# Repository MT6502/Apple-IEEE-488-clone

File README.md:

# Apple-IEEE-488-clone
the schematic is based on the original documented
in the IEEE-488 interface manual from Apple with some smaller changes, mainly for easier routing the board.
The manual can be found at several places in the internet. 
Actually the following links will work:
https://www.applefritter.com/files/2021/08/15/Apple%20%5D%5B%20___%20IEEE-488%20Interface%20Users%20Guide.pdf
the rom can be found here, no other source found yet:
https://www.applefritter.com/files/2021/09/19/Apple%20IEEE%20488%20ROM%20Dump.BIN_.zip
corosponnding chat @Applefritter:
https://www.applefritter.com/content/apple-ieee-488-interface-card

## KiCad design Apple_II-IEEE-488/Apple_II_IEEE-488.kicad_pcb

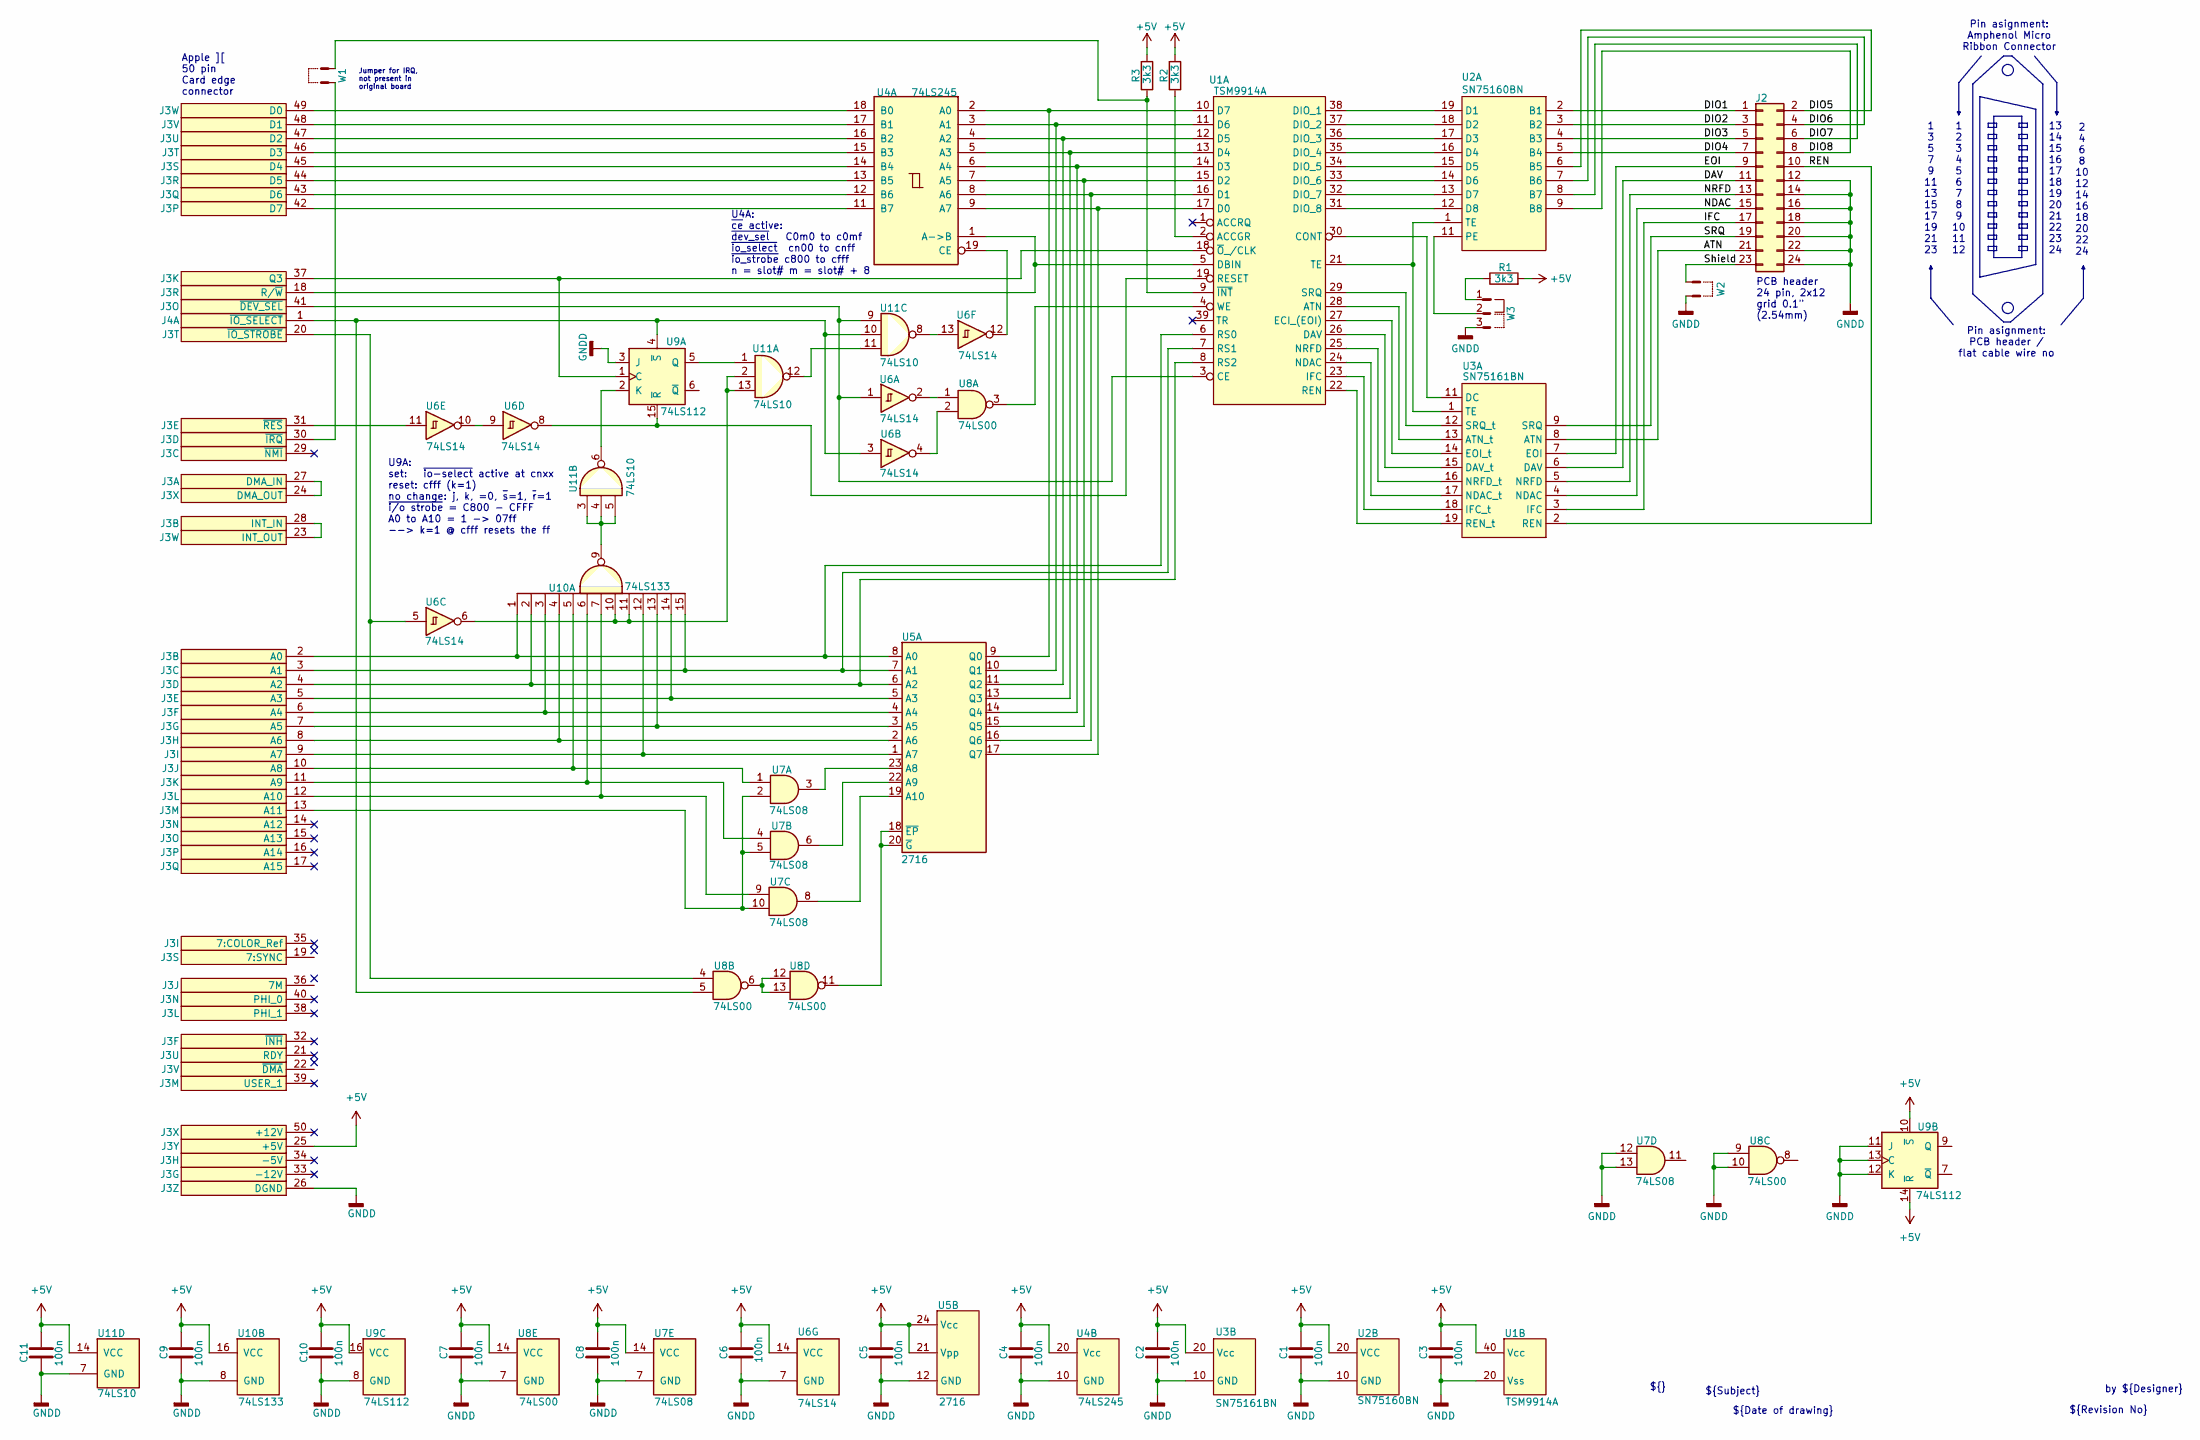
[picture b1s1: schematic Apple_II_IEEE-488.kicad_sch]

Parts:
C1, C2, C3, C4, C5, C6, C7, C8, C9, C10, C11: 100n; C_disk_2.54mm
J2: Conn_02x12_Odd_Even; IDC-Header_2x12_P2.54mm_Vertical
J3: Apple_II_card_edge
J4: (no value)
R1, R2, R3: 3k3; R_Axial_L3.6mm_D1.6mm_P2.54mm_Vertical
U1: TSM9914A; DIP-40_W15.24mm
U2: SN75160BN; DIP-20_W7.62mm
U3: SN75161BN; DIP-20_W7.62mm
U4: 74LS245; DIP-20_W7.62mm
U5: 2716; DIP-24_17.53mmx33.02mm_W15.24mm_sb
U6: 74LS14; DIP-14_W7.62mm
U7: 74LS08; DIP-14_W7.62mm
U8: 74LS00; DIP-14_W7.62mm
U9: 74LS112; DIP-16_W7.62mm
U10: 74LS133; DIP-16_W7.62mm
U11: 74LS10; DIP-14_W7.62mm
W1, W2: JP_2pin
W3: Jumper2pos

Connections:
+5V: C1.1, C2.1, C3.1, C4.1, C5.1, C6.1, C7.1, C8.1, C9.1, C10.1, C11.1, J3.25 (+5V), R1.2, R2.2, R3.2, U1.40 (Vcc), U2.20 (VCC), U3.20 (Vcc), U4.20 (Vcc), U5.21 (Vpp), U5.24 (Vcc), U6.14 (VCC), U7.14 (VCC), U8.14 (VCC), U9.10 (~S), U9.14 (~R), U9.16 (VCC), U10.16 (VCC), U11.14 (VCC)
/ATN: J2.21, U3.8 (ATN)
/DAV: J2.11, U3.6 (DAV)
/DIO1: J2.1, U2.2 (B1)
/DIO2: J2.3, U2.3 (B2)
/DIO3: J2.5, U2.4 (B3)
/DIO4: J2.7, U2.5 (B4)
/DIO5: J2.2, U2.6 (B5)
/DIO6: J2.4, U2.7 (B6)
/DIO7: J2.6, U2.8 (B7)
/DIO8: J2.8, U2.9 (B8)
/EOI: J2.9, U3.7 (EOI)
/IFC: J2.17, U3.3 (IFC)
/NDAC: J2.15, U3.4 (NDAC)
/NRFD: J2.13, U3.5 (NRFD)
/REN: J2.10, U3.2 (REN)
/SRQ: J2.19, U3.9 (SRQ)
/Shield: J2.23, W2.2
GNDD: C1.2, C2.2, C3.2, C4.2, C5.2, C6.2, C7.2, C8.2, C9.2, C10.2, C11.2, J2.12, J2.14, J2.16, J2.18, J2.20, J2.22, J2.24, J3.26 (DGND), U1.20 (Vss), U2.10 (GND), U3.10 (GND), U4.10 (GND), U5.12 (GND), U6.7 (GND), U7.7 (GND), U7.12, U7.13, U8.7 (GND), U8.9, U8.10, U9.3 (J), U9.8 (GND), U9.11 (J), U9.12 (K), U9.13 (C), U10.8 (GND), U11.7 (GND), W2.1, W3.3
unnamed: J3.24 (DMA_OUT), J3.27 (DMA_IN)
unnamed: J3.23 (INT_OUT), J3.28 (INT_IN)
unnamed: J3.30 (~IRQ), W1.1
unnamed: J3.31 (~RES), U6.11
unnamed: J3.37 (Q3), U1.18 (~O_/CLK), U9.1 (C)
unnamed: J3.41 (~DEV_SEL), U1.3 (CE), U6.1, U11.9
unnamed: J3.42 (D7), U4.11 (B7)
unnamed: J3.43 (D6), U4.12 (B6)
unnamed: J3.44 (D5), U4.13 (B5)
unnamed: J3.45 (D4), U4.14 (B4)
unnamed: J3.46 (D3), U4.15 (B3)
unnamed: J3.47 (D2), U4.16 (B2)
unnamed: J3.48 (D1), U4.17 (B1)
unnamed: J3.49 (D0), U4.18 (B0)
unnamed: J3.2 (A0), U1.6 (RS0), U5.8 (A0), U10.1
unnamed: J3.3 (A1), U1.7 (RS1), U5.7 (A1), U10.15
unnamed: J3.4 (A2), U1.8 (RS2), U5.6 (A2), U10.2
unnamed: J3.5 (A3), U5.5 (A3), U10.14
unnamed: J3.6 (A4), U5.4 (A4), U10.3
unnamed: J3.7 (A5), U5.3 (A5), U10.13
unnamed: J3.8 (A6), U5.2 (A6), U10.4
unnamed: J3.9 (A7), U5.1 (A7), U10.12
unnamed: J3.10 (A8), U7.1, U10.5
unnamed: J3.11 (A9), U7.4, U10.6
unnamed: J3.12 (A10), U7.9, U10.7
unnamed: J3.13 (A11), U7.2, U7.5, U7.10
unnamed: J3.18 (R/~W), U1.5 (DBIN), U4.1 (A->B)
unnamed: J3.20 (~IO_STROBE), U6.5, U8.4
unnamed: J4.1 (~IO_SELECT), U6.3, U8.5, U9.4 (~S), U11.10
unnamed: R1.1, W3.1
unnamed: R2.1, U1.2 (ACCGR)
unnamed: U1.28 (ATN), U3.13 (ATN_t)
unnamed: U1.30 (CONT), U3.11 (DC)
unnamed: U1.17 (D0), U4.9 (A7), U5.17 (Q7)
unnamed: U1.16 (D1), U4.8 (A6), U5.16 (Q6)
unnamed: U1.15 (D2), U4.7 (A5), U5.15 (Q5)
unnamed: U1.14 (D3), U4.6 (A4), U5.14 (Q4)
unnamed: U1.13 (D4), U4.5 (A3), U5.13 (Q3)
unnamed: U1.12 (D5), U4.4 (A2), U5.11 (Q2)
unnamed: U1.11 (D6), U4.3 (A1), U5.10 (Q1)
unnamed: U1.10 (D7), U4.2 (A0), U5.9 (Q0)
unnamed: U1.26 (DAV), U3.15 (DAV_t)
unnamed: U1.38 (DIO_1), U2.19 (D1)
unnamed: U1.37 (DIO_2), U2.18 (D2)
unnamed: U1.36 (DIO_3), U2.17 (D3)
unnamed: U1.35 (DIO_4), U2.16 (D4)
unnamed: U1.34 (DIO_5), U2.15 (D5)
unnamed: U1.33 (DIO_6), U2.14 (D6)
unnamed: U1.32 (DIO_7), U2.13 (D7)
unnamed: U1.31 (DIO_8), U2.12 (D8)
unnamed: U1.27 (ECI_(EOI)), U3.14 (EOI_t)
unnamed: U1.23 (IFC), U3.18 (IFC_t)
unnamed: U1.24 (NDAC), U3.17 (NDAC_t)
unnamed: U1.25 (NRFD), U3.16 (NRFD_t)
unnamed: U1.22 (REN), U3.19 (REN_t)
unnamed: U1.19 (RESET), U6.8, U9.15 (~R)
unnamed: U1.29 (SRQ), U3.12 (SRQ_t)
unnamed: U1.21 (TE), U2.1 (TE), U3.1 (TE)
unnamed: U1.4 (WE), U8.3
unnamed: R3.1, U1.9 (~INT), W1.2
unnamed: U2.11 (PE), W3.2
unnamed: U4.19 (CE), U6.12
unnamed: U5.23 (A8), U7.3
unnamed: U5.22 (A9), U7.6
unnamed: U5.19 (A10), U7.8
unnamed: U5.18 (~EP), U5.20 (~G), U8.11
unnamed: U6.2, U8.1
unnamed: U6.4, U8.2
unnamed: U6.9, U6.10
unnamed: U8.6, U8.12, U8.13
unnamed: U9.2 (K), U11.6
unnamed: U9.5 (Q), U11.1
unnamed: U10.9, U11.3, U11.4, U11.5
unnamed: U6.6, U10.10, U10.11, U11.2, U11.13
unnamed: U6.13, U11.8
unnamed: U11.11, U11.12

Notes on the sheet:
2 4 6 8 10 12 14 16 18 20 22 24
1 2 3 4 5 6 7 8 9 10 11 12
${Date of drawing}
U4A: ~{ce} active: ~{dev_sel} C0m0 to c0mf ~{io_select} cn00 to cnff ~{io_strobe} c800 to cfff n = slot# m = slot# + 8
13 14 15 16 17 18 19 20 21 22 23 24
PCB header 24 pin, 2x12 grid 0.1" (2.54mm)
Apple ][ 50 pin Card edge connector
by ${Designer}
${Subject}
1 3 5 7 9 11 13 15 17 19 21 23
${Revision No}
U9A: set: ~{io-select} active at cnxx reset: cfff (k=1) no change: j, k, =0, ~{s}=1, ~{r}=1 ~{i/o strobe} = C800 - CFFF A0 to A10 = 1 -> 07ff --> k=1 @ cfff resets the ff
${}
Pin asignment: Amphenol Micro Ribbon Connector
Pin asignment: PCB header / flat cable wire no
Jumper for IRQ, not present in original board

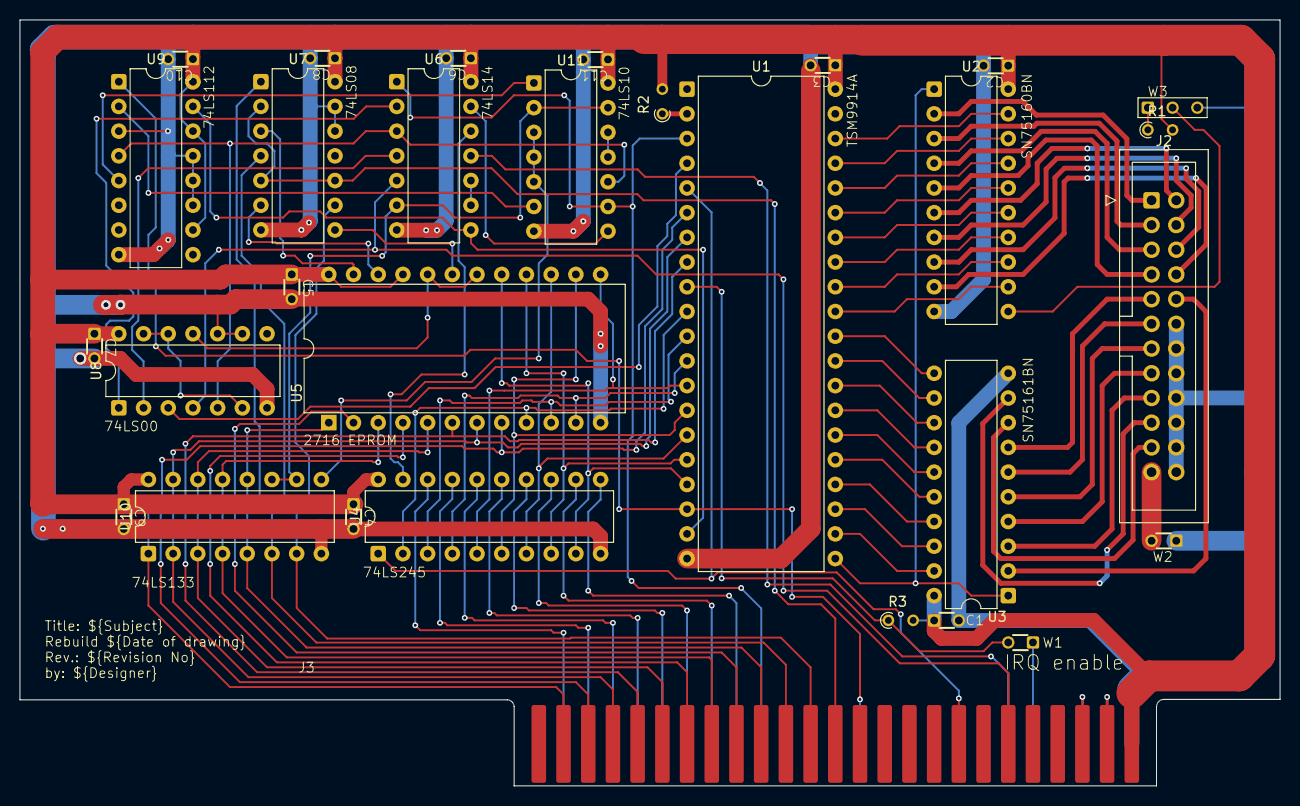
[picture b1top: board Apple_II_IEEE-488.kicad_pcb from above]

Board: 2 copper layers, 129.5 x 78.7 mm, 30 parts (0 on the bottom side), 95 nets.
